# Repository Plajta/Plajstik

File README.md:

# plajstik
One-handed joystick for disabled people

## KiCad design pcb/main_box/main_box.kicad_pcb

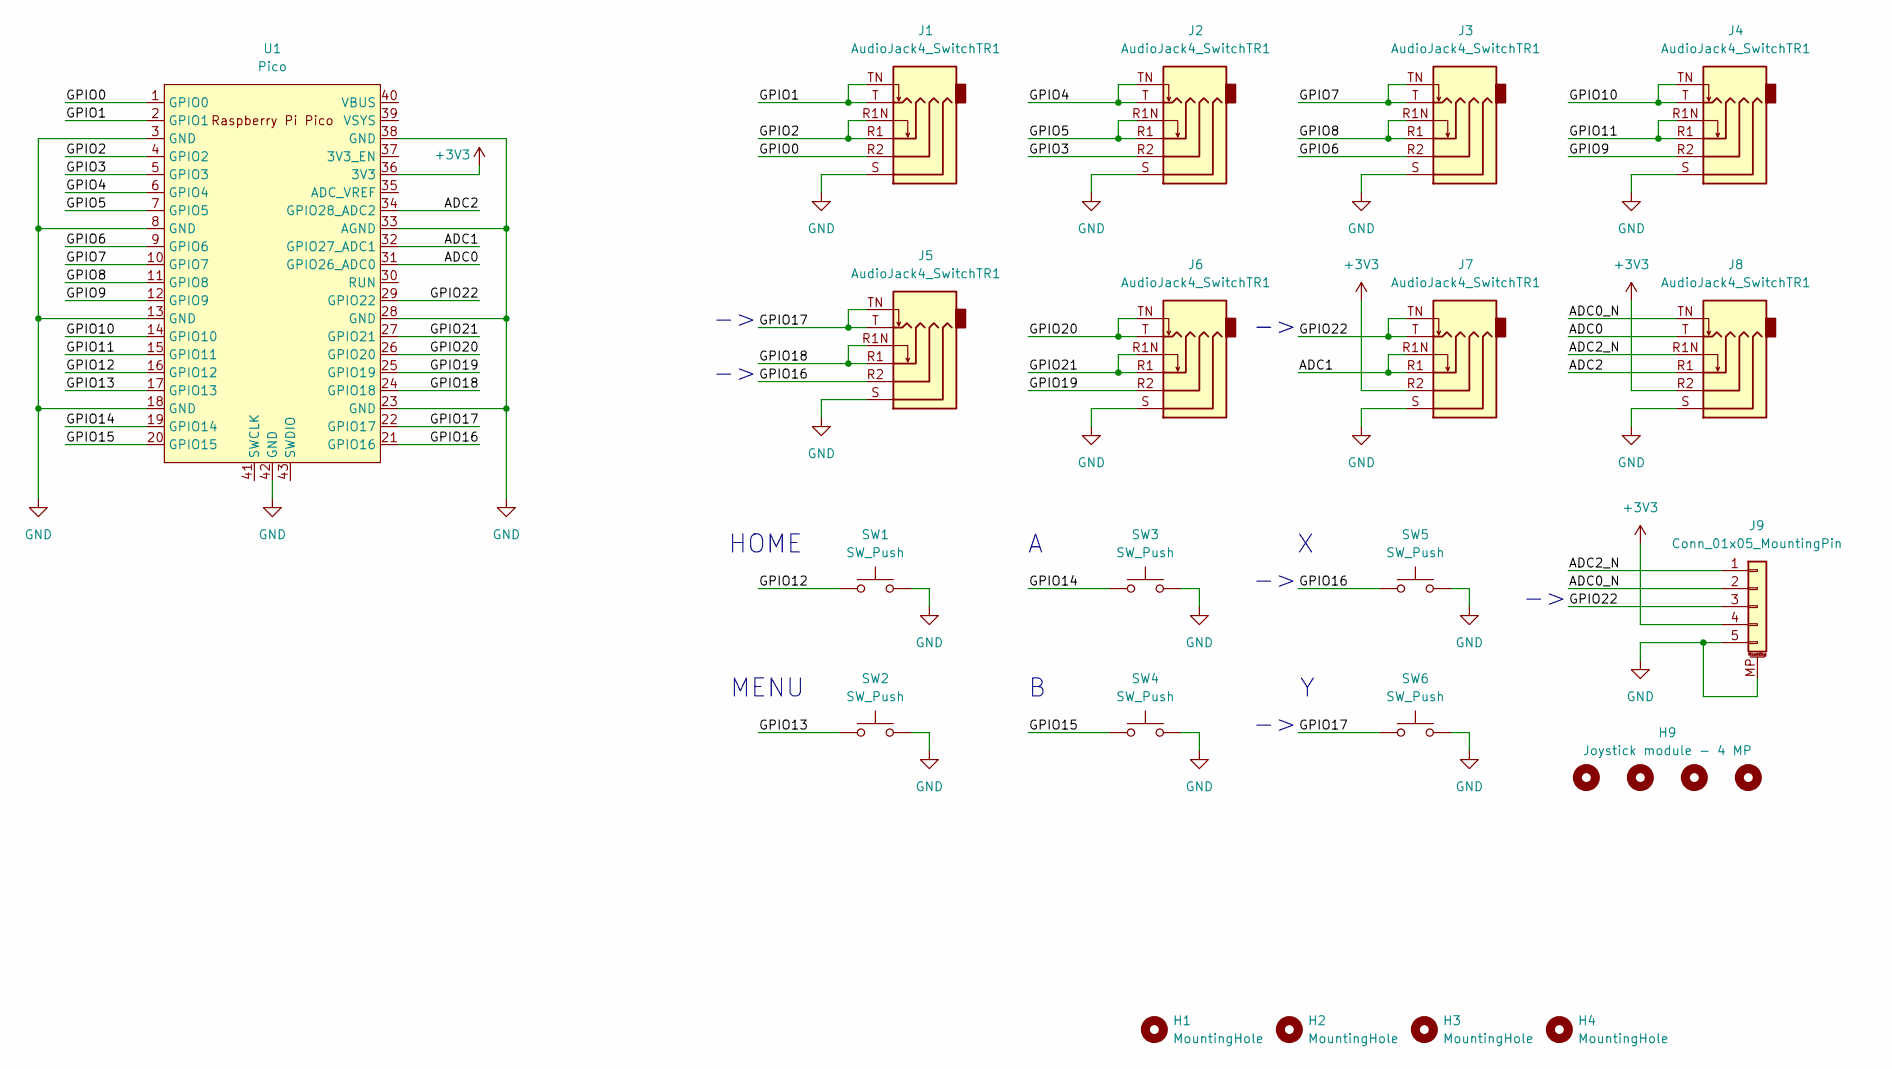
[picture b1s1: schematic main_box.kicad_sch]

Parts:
H1, H2, H3, H4: MountingHole; MountingHole_3.2mm_M3
H9: Joystick module - 4 MP; Joystick_module_lifted
J1, J2, J3, J4, J5, J6, J7, J8: AudioJack4_SwitchTR1; Jack_3.5_PJ31060-I_L_pads
J9: Conn_01x05_MountingPin; JST_XH_S5B_combined_1x05
SW1, SW2, SW3, SW4, SW5, SW6: SW_Push; SW_PUSH_combined_6mm
U1: Pico; RPi_Pico_SMD_TH

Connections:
+3V3: J7.R2, J8.R2, J9.4, U1.36 (3V3)
/ADC0: J8.T, U1.31 (GPIO26_ADC0)
/ADC0_N: J8.TN, J9.2
/ADC1: J7.R1, J7.R1N, U1.32 (GPIO27_ADC1)
/ADC2: J8.R1, U1.34 (GPIO28_ADC2)
/ADC2_N: J8.R1N, J9.1
/GPIO0: J1.R2, U1.1 (GPIO0)
/GPIO1: J1.T, J1.TN, U1.2 (GPIO1)
/GPIO2: J1.R1, J1.R1N, U1.4 (GPIO2)
/GPIO3: J2.R2, U1.5 (GPIO3)
/GPIO4: J2.T, J2.TN, U1.6 (GPIO4)
/GPIO5: J2.R1, J2.R1N, U1.7 (GPIO5)
/GPIO6: J3.R2, U1.9 (GPIO6)
/GPIO7: J3.T, J3.TN, U1.10 (GPIO7)
/GPIO8: J3.R1, J3.R1N, U1.11 (GPIO8)
/GPIO9: J4.R2, U1.12 (GPIO9)
/GPIO10: J4.T, J4.TN, U1.14 (GPIO10)
/GPIO11: J4.R1, J4.R1N, U1.15 (GPIO11)
/GPIO12: SW1.1, U1.16 (GPIO12)
/GPIO13: SW2.1, U1.17 (GPIO13)
/GPIO14: SW3.1, U1.19 (GPIO14)
/GPIO15: SW4.1, U1.20 (GPIO15)
/GPIO16: J5.R2, SW5.1, U1.21 (GPIO16)
/GPIO17: J5.T, J5.TN, SW6.1, U1.22 (GPIO17)
/GPIO18: J5.R1, J5.R1N, U1.24 (GPIO18)
/GPIO19: J6.R2, U1.25 (GPIO19)
/GPIO20: J6.T, J6.TN, U1.26 (GPIO20)
/GPIO21: J6.R1, J6.R1N, U1.27 (GPIO21)
/GPIO22: J7.T, J7.TN, J9.3, U1.29 (GPIO22)
GND: J1.S, J2.S, J3.S, J4.S, J5.S, J6.S, J7.S, J8.S, J9.5, J9.MP (MountPin), SW1.2, SW2.2, SW3.2, SW4.2, SW5.2, SW6.2, U1.3 (GND), U1.8 (GND), U1.13 (GND), U1.18 (GND), U1.23 (GND), U1.28 (GND), U1.33 (AGND), U1.38 (GND), U1.42 (GND)

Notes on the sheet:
HOME
MENU

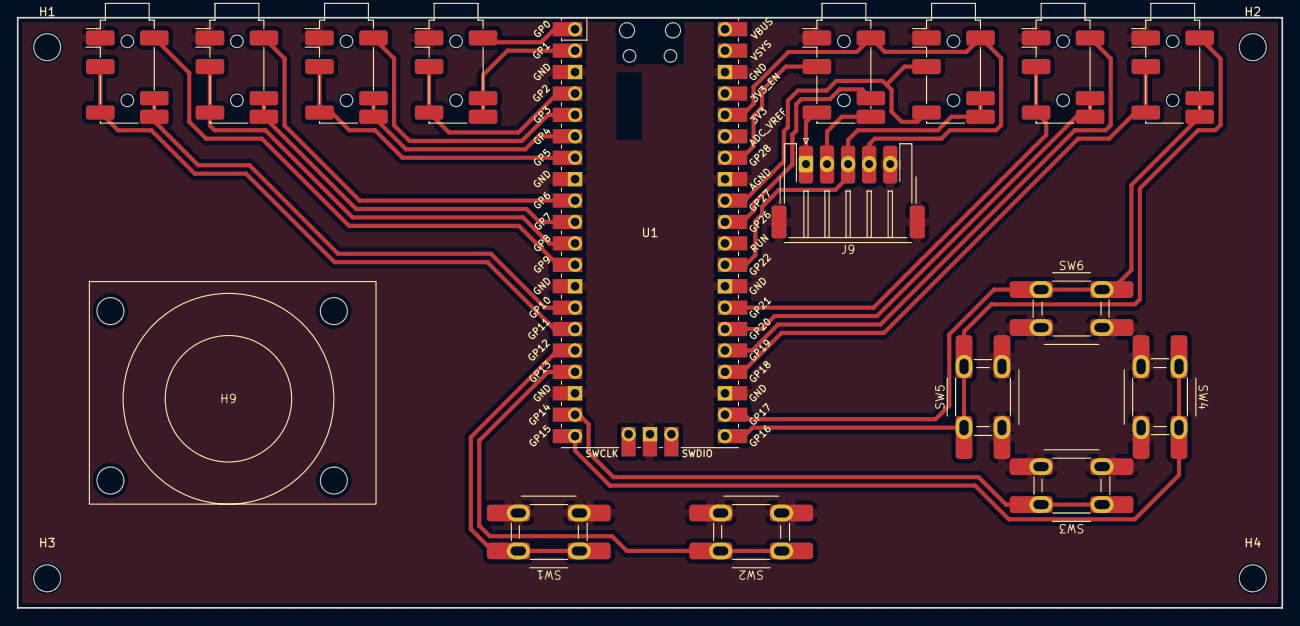
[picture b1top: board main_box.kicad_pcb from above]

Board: 2 copper layers, 150.0 x 70.0 mm, 21 parts (0 on the bottom side), 30 nets.

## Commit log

2024-03-08 Lolik, first cmmitik...
2024-03-08 idea do ignoru
2024-03-08 zakladni tauri project setup
2024-03-08 debloat konfiguratoru a editorconfig pro konfigurator
2024-03-08 dalsi debloat a nejaky styly
2024-03-08 first floor is done so i can go sleep
2024-03-08 shadcnui pridano do konfiguratoru
2024-03-08 dark mod a i ten white mod
2024-03-08 zmena nazvu vokna apliakce
2024-03-08 jina pozice theme switcheru a kontentu stranky
2024-03-09 zakladni visualizace joysticku
2024-03-09 spravnej zindex na theme switcher
2024-03-09 Kinda made controller work...
2024-03-09 3d labely goes brrrrr
2024-03-09 chuvjovina od macu do ignoru
2024-03-09 kell mi plase
2024-03-09 actually joystick model
2024-03-09 velikost fontu a padding u labelu
2024-03-09 zakladni dialog na konfiguraci tlacitek
2024-03-09 zindx na dialog
2024-03-09 prevenece overflowu
2024-03-09 odjebani dialogu
2024-03-09 zakladno button label
2024-03-09 cary a styly button labelu
2024-03-09 hezcejsi styl na cary v labelu
2024-03-09 kompletni refactor systemu na otevrinai menucek
2024-03-09 zbytecnej import
2024-03-09 Updated firmware Still needs some work but that isn't that urgent
2024-03-09 zakladni strukcutra keybind menu
2024-03-09 schopna cara
2024-03-09 actually keybindy
2024-03-09 jmena tlacitek jako ame a label v konstantach
2024-03-09 rozsireni labelu
2024-03-09 Lolik, broucek zmizel :)
2024-03-09 cara styly
2024-03-09 konecne to bypada celkem dobre
2024-03-09 Fix USB YAAAAAAAAAY, IT TOTALLY DIDN'T TAKE 4 HOURS OF TWO PEOPLE
2024-03-09 Add tiny-json and broken serial
2024-03-09 brani keymapu z rust backendu
2024-03-09 ikona u vbraneho keybinfdu
2024-03-09 Add more buttons
2024-03-09 Fix typo
2024-03-09 selectovani novejch hodnot
2024-03-09 pointer
2024-03-09 akce na ukladani keymapy a rust parser na parametry
2024-03-09 SERIAL LOOPBACK WORX NO WAY, I ACTUALLY WANT TO CRY RIGHT NOW
2024-03-09 so all is designed
2024-03-09 novej format configuracniho jsonu
2024-03-09 akce a reakce
2024-03-09 nova akce
2024-03-09 pokus cislo 3
2024-03-09 vole novejsi node
2024-03-09 nevim uz
2024-03-10 kradez neuspesna
2024-03-10 Umm base...
2024-03-10 Please work We gonna go to sleep
2024-03-10 vlevo hled
2024-03-10 nahoru hled
2024-03-10 pozice lepsi
2024-03-10 dopad konstanta
2024-03-10 keymapa z rustu posilana
2024-03-10 officialni nejlepsi programator
2024-03-10 finalni upravy
2024-03-10 Swap axis, fix bugs And cleanup
2024-03-27 Cleanup Another cleanup is coming
2024-04-09 Cleanup and default config Default config that actually works? No way!
2024-04-29 [WIP] Add persisent storage The code locks up, it still needs to fix some bugs. And it is also messy And I don't like it And... And...
2024-05-05 Persistent storage now works Still neeeds testing but it seems that I finally got i to work, i am SO happy.
2024-05-05 More clean saving Still need to make the JSON from USB persistent
2024-05-05 Fully working persistent storage! The code is due for a cleanup, that will be the next thing on my list
2024-05-06 [WIP] Code cleanup
2024-05-19 Remove more unnecessary lines
2024-05-19 Add a few comments
2024-05-19 [WIP] Add deadzone Not fully implemented deadzone is already there, but it unfortunately is a square deadzone. Better implementation is on it's way
2024-05-28 A better deadzone
2024-06-02 Reworked JSON config This commit is made up of the following commits:
    commit e6ee77a4e78b60883215755a2f19e471040667e0
    Author: Vesek <venda.straka@gmail.com>
    Date: Sun Jun 2 13:58:52 2024 +0200
    JSON rewrite now works
    commit ac66a50fac0ac6bfe693af5c68d15848674cf699
    Author: Vesek <venda.straka@gmail.com>
2024-06-02 Cleanup, remove unused includes
2024-06-02 Add deadzone config to JSON Small cleanup Deadzone can now be configured from the JSON config
2024-06-02 Fix default json Deadzone was an integer, not a real number
2024-06-02 Add ADC to JSON ADC can now be configured from the config JSON
2024-06-03 Change default deadzone to 0
2024-06-03 Add docs for JSON config
2024-07-07 Make Pico SDK download itself using cmake
2024-07-07 Add loading of saved config JSON + bunch of fixes The config JSON saved in the board's flash can now recalled over serial with sending `load` and "End of transmission" (on Linux CTRL+D, 0x04 hexadeci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
2024-07-07 Add warning of buffer overflow on serial input
2024-08-05 Add a fully configured JSON as an example
2024-09-23 Some fixes for 3D model
2024-10-07 editor
2024-10-21 peer deps
2024-10-21 zatim smazat model canvas
2024-10-21 baliky
2024-11-26 Add analog axes multiplier Restructure source
2024-12-09 Add docs for configuring and multiplier
2024-12-09 Fix wrongly bolded text
2024-12-09 Fix for fix of wrongly bolded text
2025-01-18 WIP - main box PCB
2025-01-18 Mby somewhat done...
2025-01-19 Redesigned gimbal housing
2025-01-20 Commiting this in case I do something horribly wrong
2025-01-22 Getting there, just buttons are still small...
2025-01-22 Maybe done, but some refactoring is needed
2025-01-24 Project fix and some 3D changes
2025-02-06 Had to speedrun changing footprint of jacks, laskakit had wrong part number on their site...
2025-02-23 Some stability improvements
2025-02-24 New joystick concept, Some fixes in housing model
2025-02-25 Trying some more organic shapes
2025-03-10 Update pico_sdk_import They added a license to it so that's fair cmake was also getting grumpy because it was old
2025-03-10 Small cleanup of weird lookup Also fix for Clangd
2025-03-10 Add some missing(?) includes
2025-03-10 Rewrite pin mapping Now binds buttons to pins, not pins to buttons, so you can have for example pin 2 and 4 press the button A.
    Some fixes
    New JSON version
2025-03-13 Fix device descriptor name
2025-03-24 some 3d improvements and added PDF scheme
2025-03-31 Update default config
